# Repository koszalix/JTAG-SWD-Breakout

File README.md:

# JTAG/SWD Breakout

Simple breakout board for [10 Pin JTAG interface](https://developer.arm.com/documentation/101416/0100/Hardware-Description/Target-Interfaces/Cortex-Debug--10-pin-).

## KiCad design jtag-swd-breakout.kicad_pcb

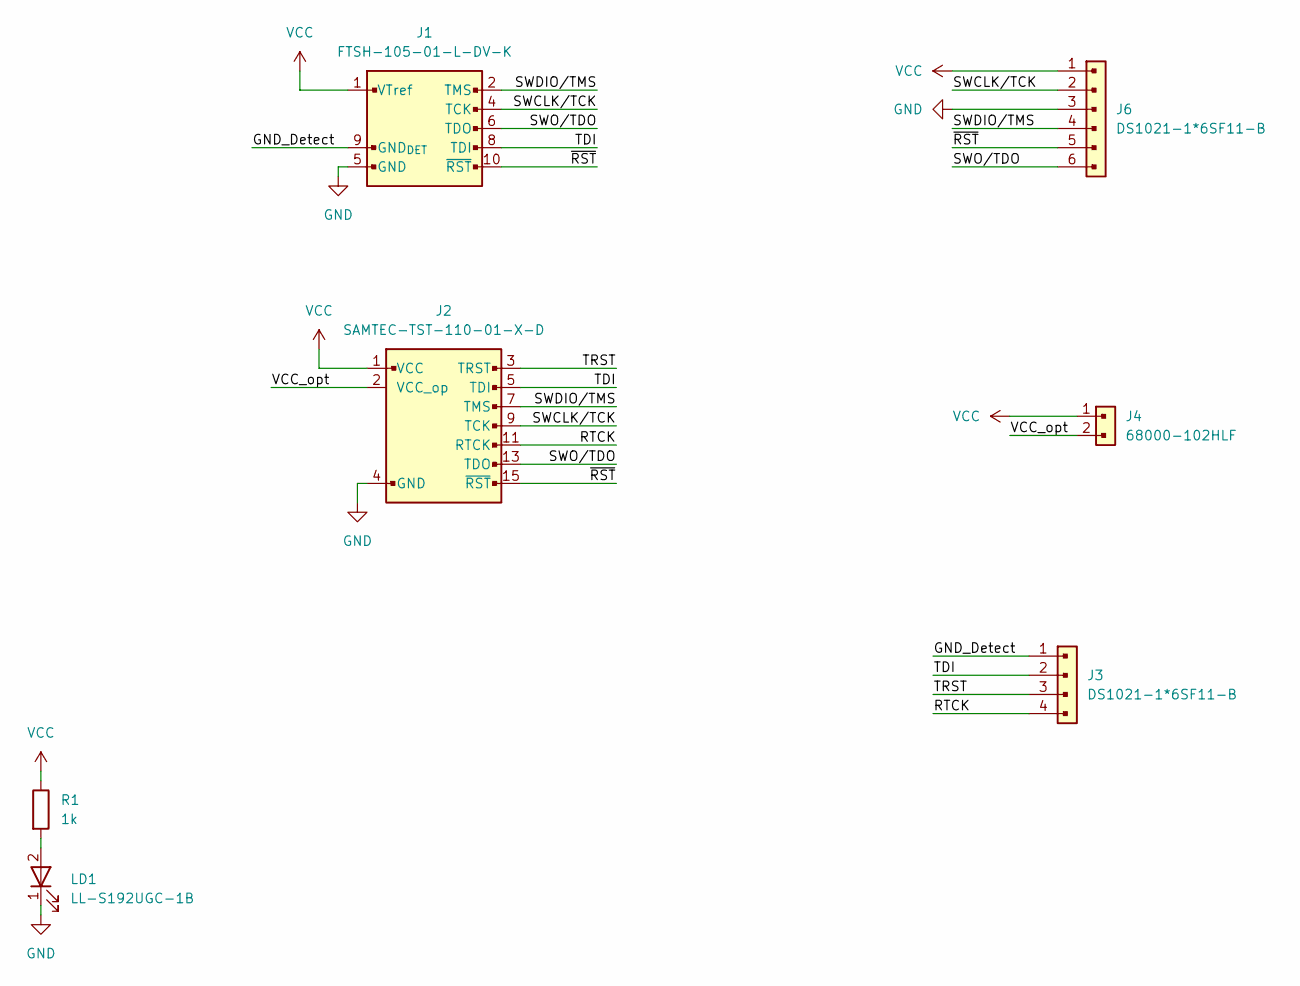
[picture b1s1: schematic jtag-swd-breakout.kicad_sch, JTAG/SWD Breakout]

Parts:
J1: JTAG; Samtec-FTSH-105-01-L-DV-K; MPN FTSH-105-01-L-DV-K
J2: SAMTEC-TST-110-01-X-D; MPN SAMTEC-TST-110-01-X-D
J3: DS1021-1*4SF11-B; PinHeader_1x04_P2.54mm_Vertical; MPN DS1021-1*6SF11-B
J4: 68000-102HLF; Amphenol_68000_102HLF; MPN 68000-102HLF
J6: DS1021-1*6SF11-B; PinHeader_1x06_P2.54mm_Vertical; MPN DS1021-1*6SF11-B
LD1: LL-S192UGC-1B; LED_0603_1608Metric; MPN LL-S192UGC-1B
R1: 1k; R_0603_1608Metric; Tolerance 1%; MPN RC0603FR-071k

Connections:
/GND_Detect: J1.9 (GND_{DET}), J3.1
/RTCK: J2.11 (RTCK), J3.4
/SWCLK/TCK: J1.4 (TCK), J2.9 (TCK), J6.2
/SWDIO/TMS: J1.2 (TMS), J2.7 (TMS), J6.4
/SWO/TDO: J1.6 (TDO), J2.13 (TDO), J6.6
/TDI: J1.8 (TDI), J2.5 (TDI), J3.2
/TRST: J2.3 (TRST), J3.3
/VCC_opt: J2.2 (VCC_op), J4.2
/~RST: J1.10 (~RST), J2.15 (~RST), J6.5
GND: J1.3 (GND), J1.5 (GND), J2.4 (GND), J2.6 (GND), J2.8 (GND), J2.10 (GND), J2.12 (GND), J2.14 (GND), J2.16 (GND), J2.18 (GND), J2.20 (GND), J6.3, LD1.1
unnamed: LD1.2, R1.2
VCC: J1.1 (VTref), J2.1 (VCC), J4.1, J6.1, R1.1

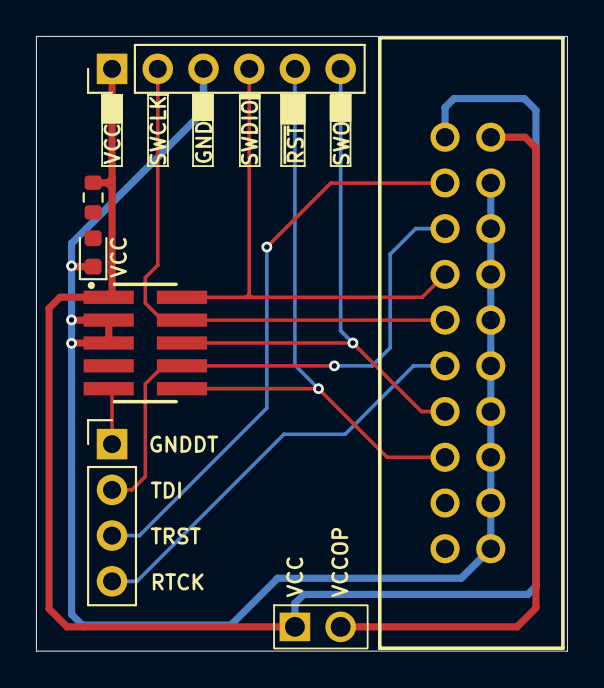
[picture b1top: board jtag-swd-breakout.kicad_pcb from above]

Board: 2 copper layers, 29.5 x 34.1 mm, 7 parts (0 on the bottom side), 12 nets.

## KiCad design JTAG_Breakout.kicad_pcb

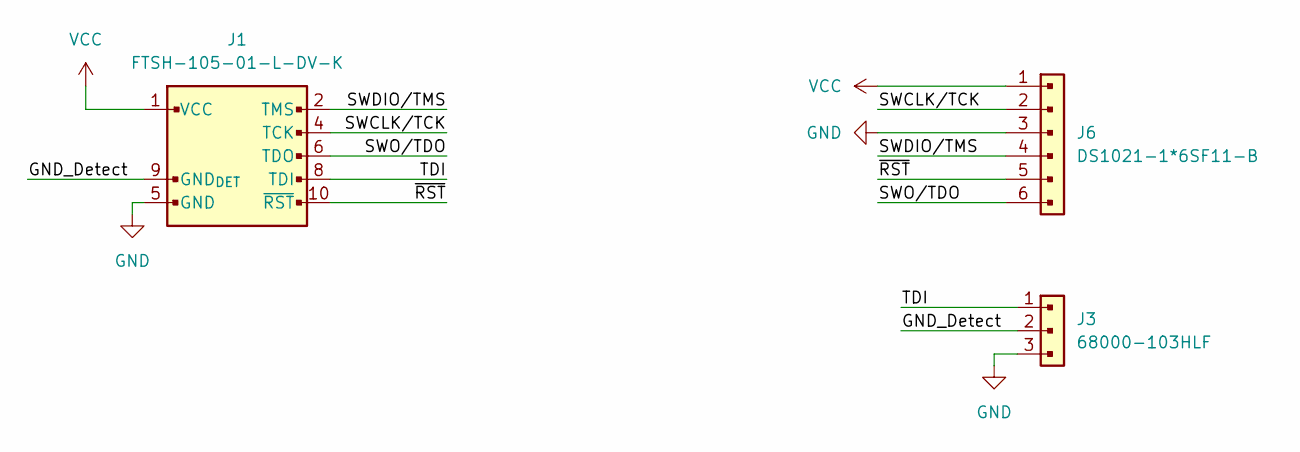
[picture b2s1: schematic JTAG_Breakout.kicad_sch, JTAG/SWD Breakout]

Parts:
J1: JTAG; Samtec-FTSH-105-01-L-DV-K; MPN FTSH-105-01-L-DV-K
J3: 68000-103HLF; Amphenol_68000-103HLF; MPN 68000-103HLF
J6: DS1021-1*6SF11-B; PinHeader_1x06_P2.54mm_Vertical; MPN DS1021-1*6SF11-B

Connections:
/GND_Detect: J1.9 (GND_{DET}), J3.2
/SWCLK/TCK: J1.4 (TCK), J6.2
/SWDIO/TMS: J1.2 (TMS), J6.4
/SWO/TDO: J1.6 (TDO), J6.6
/TDI: J1.8 (TDI), J3.1
/~RST: J1.10 (~RST), J6.5
GND: J1.3 (GND), J1.5 (GND), J3.3, J6.3
VCC: J1.1 (VCC), J6.1

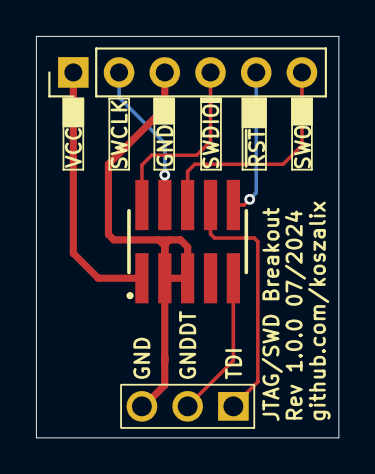
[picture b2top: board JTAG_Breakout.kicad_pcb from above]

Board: 2 copper layers, 16.8 x 22.3 mm, 3 parts (0 on the bottom side), 8 nets.

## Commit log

2024-07-20 Prepare schematic
2024-07-20 Route PCB
2024-07-20 Add git ignore
2024-07-20 Rename project
2024-07-20 Add readme
2024-07-27 Add JTAG 20
2024-11-17 Update adapter
